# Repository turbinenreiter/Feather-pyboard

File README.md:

# Feather-pyboard

A STM32F411 development board compatible with the Feather form factor and designed to run MicroPython.

*NOTE: The desing is as of yet untested.*

This design heavily leans on [Adafruit Feather M0 Adalogger](https://github.com/adafruit/Adafruit-Feather-M0-Adalogger-PCB), [MicroPython pyboard](https://github.com/micropython/pyboard) and [Espruino Pico](https://github.com/espruino/EspruinoBoard/tree/master/Pico).

[Creative Commons Attribution, Share-Alike license](https://creativecommons.org/licenses/by/4.0)

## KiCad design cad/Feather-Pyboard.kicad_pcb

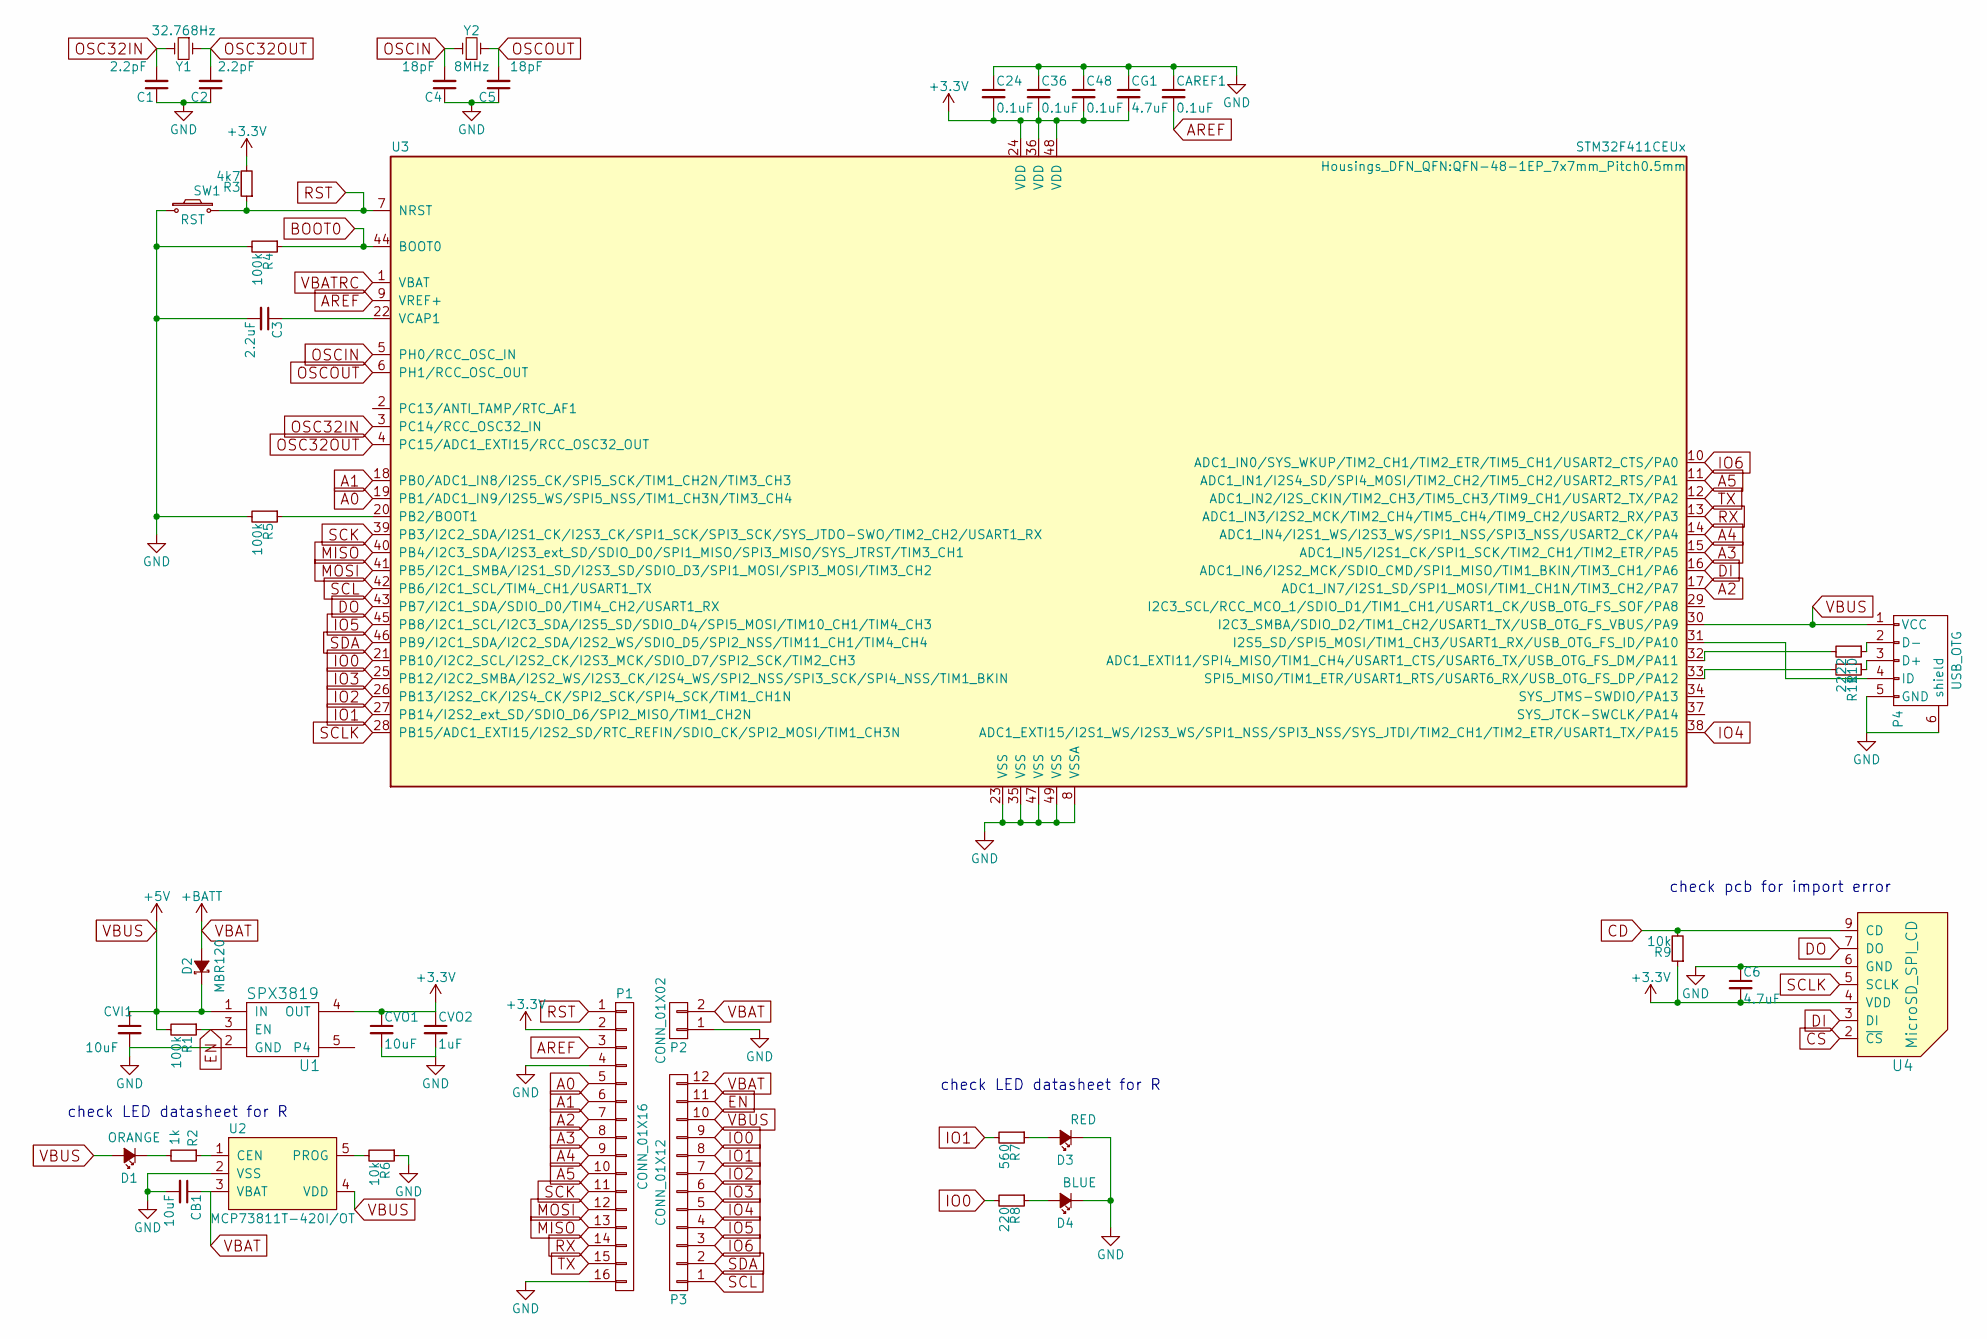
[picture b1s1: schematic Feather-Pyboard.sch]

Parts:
C1, C2: 2.2pF; C_0402
C3: 2.2uF; C_0402
C4, C5: 18pF; C_0402
C6: 4.7uF; C_0402
C24, C36, C48: 0.1uF; C_0402
CAREF1: 0.1uF; C_0402
CB1: 10uF; C_0402
CG1: 4.7uF; C_0402
CVI1: 10uF; C_0402
CVO1: 10uF; C_0402
CVO2: 1uF; C_0402
D1: ORANGE; LED_0402
D2: MBR120; SOD-123
D3: RED; LED_0402
D4: BLUE; LED_0402
P1: CONN_01X16; Socket_Strip_Straight_1x16
P2: CONN_01X02; JST_PH_S2B-PH-SM4-TB_02x2.00mm_Angled
P3: CONN_01X12; Socket_Strip_Straight_1x12
P4: USB_OTG; USB_Micro-B
R1, R4, R5: 100k; R_0402
R2: 1k; R_0402
R3: 4k7; R_0402
R6, R9: 10k; R_0402
R7: 560; R_0402
R8: 220; R_0402
R10, R11: 22; R_0402
SW1: RST; SW_SPST_B3U-1000P
U1: SPX3819; SOT-23-5
U2: MCP73811T-420I/OT; SOT-23-5
U3: STM32F411CEUx; QFN-48-1EP_7x7mm_Pitch0.5mm
U4: MicroSD_SPI_CD; HIROSE-MICROSD-DM3AT-SF
Y1: 32.768Hz; R-0805
Y2: 8MHz; Crystal_SMD_ABM3B

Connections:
+3V3: C6.2, C24.2, C36.2, C48.2, CG1.2, CVO1.1, CVO2.1, P1.2, R3.2, R9.1, U1.4 (OUT), U3.24 (VDD), U3.36 (VDD), U3.48 (VDD), U4.4 (VDD)
A0: P1.5, U3.19 (PB1/ADC1_IN9/I2S5_WS/SPI5_NSS/TIM1_CH3N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)
A1: P1.6, U3.18 (PB0/ADC1_IN8/I2S5_CK/SPI5_SCK/TIM1_CH2N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)
A2: P1.7, U3.17 (ADC1_IN7/I2S1_SD/SPI1_MOSI/TIM1_CH1N/TI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)
A3: P1.8, U3.15 (ADC1_IN5/I2S1_CK/SPI1_SCK/TIM2_CH1/TIM2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)
A4: P1.9, U3.14 (ADC1_IN4/I2S1_WS/I2S3_WS/SPI1_NSS/SPI3_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)
A5: P1.10, U3.11 (ADC1_IN1/I2S4_SD/SPI4_MOSI/TIM2_CH2/TIM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)
AREF: CAREF1.2, P1.3, U3.9 (VREF+)
BOOT0: R4.1, U3.44 (BOOT0)
CD: R9.2, U4.9 (CD)
CS: U4.2 (~CS)
DI: U3.16 (ADC1_IN6/I2S2_MCK/SDIO_CMD/SPI1_MISO/TI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), U4.3 (DI)
DO: U3.43 (PB7/I2C1_SDA/SDIO_D0/TIM4_CH2/USART1_RX), U4.7 (DO)
EN: P3.11, R1.1, U1.3 (EN)
GND: C1.1, C2.1, C3.2, C4.1, C5.1, C6.1, C24.1, C36.1, C48.1, CAREF1.1, CB1.2, CG1.1, CVI1.2, CVO1.2, CVO2.2, D3.1 (K), D4.1 (K), P1.4, P1.16, P2.1, P4.5 (GND), P4.6 (shield), R4.2, R5.2, R6.1, SW1.1, U1.2 (GND), U2.2 (VSS), U3.8 (VSSA), U3.23 (VSS), U3.35 (VSS), U3.47 (VSS), U3.49 (VSS), U4.6 (GND)
IO0: P3.9, R8.2, U3.21 (PB10/I2C2_SCL/I2S2_CK/I2S3_MCK/SDIO_D7/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)
IO1: P3.8, R7.2, U3.27 (PB14/I2S2_ext_SD/SDIO_D6/SPI2_MISO/TIM1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)
IO2: P3.7, U3.26 (PB13/I2S2_CK/I2S4_CK/SPI2_SCK/SPI4_SCK/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)
IO3: P3.6, U3.25 (PB12/I2C2_SMBA/I2S2_WS/I2S3_CK/I2S4_WS/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)
IO4: P3.5, U3.38 (ADC1_EXTI15/I2S1_WS/I2S3_WS/SPI1_NSS/SP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)
IO5: P3.4, U3.45 (PB8/I2C1_SCL/I2C3_SDA/I2S5_SD/SDIO_D4/S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)
IO6: P3.3, U3.10 (ADC1_IN0/SYS_WKUP/TIM2_CH1/TIM2_ETR/TIM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)
MISO: P1.13, U3.40 (PB4/I2C3_SDA/I2S3_ext_SD/SDIO_D0/SPI1_M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)
MOSI: P1.12, U3.41 (PB5/I2C1_SMBA/I2S1_SD/I2S3_SD/SDIO_D3/S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)
unnamed: C3.1, U3.22 (VCAP1)
unnamed: D1.1 (K), R2.2
unnamed: D3.2 (A), R7.1
unnamed: D4.2 (A), R8.1
unnamed: P4.2 (D-), R10.1
unnamed: P4.3 (D+), R11.1
unnamed: P4.4 (ID), U3.31 (I2S5_SD/SPI5_MOSI/TIM1_CH3/USART1_RX/US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)
unnamed: R2.1, U2.1 (CEN)
unnamed: R5.1, U3.20 (PB2/BOOT1)
unnamed: R6.2, U2.5 (PROG)
unnamed: R10.2, U3.32 (ADC1_EXTI11/SPI4_MISO/TIM1_CH4/USART1_C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)
unnamed: R11.2, U3.33 (SPI5_MISO/TIM1_ETR/USART1_RTS/USART6_RX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)
OSC32IN: C1.2, U3.3 (PC14/RCC_OSC32_IN), Y1.2
OSC32OUT: C2.2, U3.4 (PC15/ADC1_EXTI15/RCC_OSC32_OUT), Y1.1
OSCIN: C4.2, U3.5 (PH0/RCC_OSC_IN), Y2.1
OSCOUT: C5.2, U3.6 (PH1/RCC_OSC_OUT), Y2.2
RST: P1.1, R3.1, SW1.2, U3.7 (NRST)
RX: P1.14, U3.13 (ADC1_IN3/I2S2_MCK/TIM2_CH4/TIM5_CH4/TIM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)
SCK: P1.11, U3.39 (PB3/I2C2_SDA/I2S1_CK/I2S3_CK/SPI1_SCK/S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)
SCL: P3.1, U3.42 (PB6/I2C1_SCL/TIM4_CH1/USART1_TX)
SCLK: U3.28 (PB15/ADC1_EXTI15/I2S2_SD/RTC_REFIN/SDIO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), U4.5 (SCLK)
SDA: P3.2, U3.46 (PB9/I2C1_SDA/I2C2_SDA/I2S2_WS/SDIO_D5/S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)
TX: P1.15, U3.12 (ADC1_IN2/I2S_CKIN/TIM2_CH3/TIM5_CH3/TIM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)
VBAT: CB1.1, D2.2 (A), P2.2, P3.12, U2.3 (VBAT)
VBATRC: U3.1 (VBAT)
VBUS: CVI1.1, D1.2 (A), D2.1 (K), P3.10, P4.1 (VCC), R1.2, U1.1 (IN), U2.4 (VDD), U3.30 (I2C3_SMBA/SDIO_D2/TIM1_CH2/USART1_TX/US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)

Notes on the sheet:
check LED datasheet for R
check pcb for import error

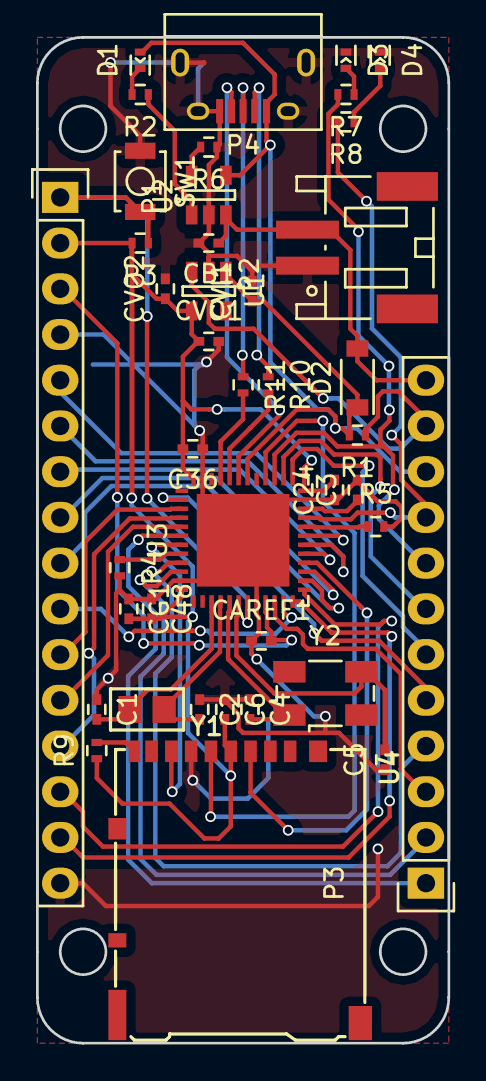
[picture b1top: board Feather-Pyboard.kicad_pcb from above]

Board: 2 copper layers, 22.9 x 55.9 mm, 41 parts (0 on the bottom side), 48 nets.

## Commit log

2016-11-01 initial commit for review
2016-11-01 added render
2016-11-02 new crystal footrpints and 22 ohm resistors for usb
